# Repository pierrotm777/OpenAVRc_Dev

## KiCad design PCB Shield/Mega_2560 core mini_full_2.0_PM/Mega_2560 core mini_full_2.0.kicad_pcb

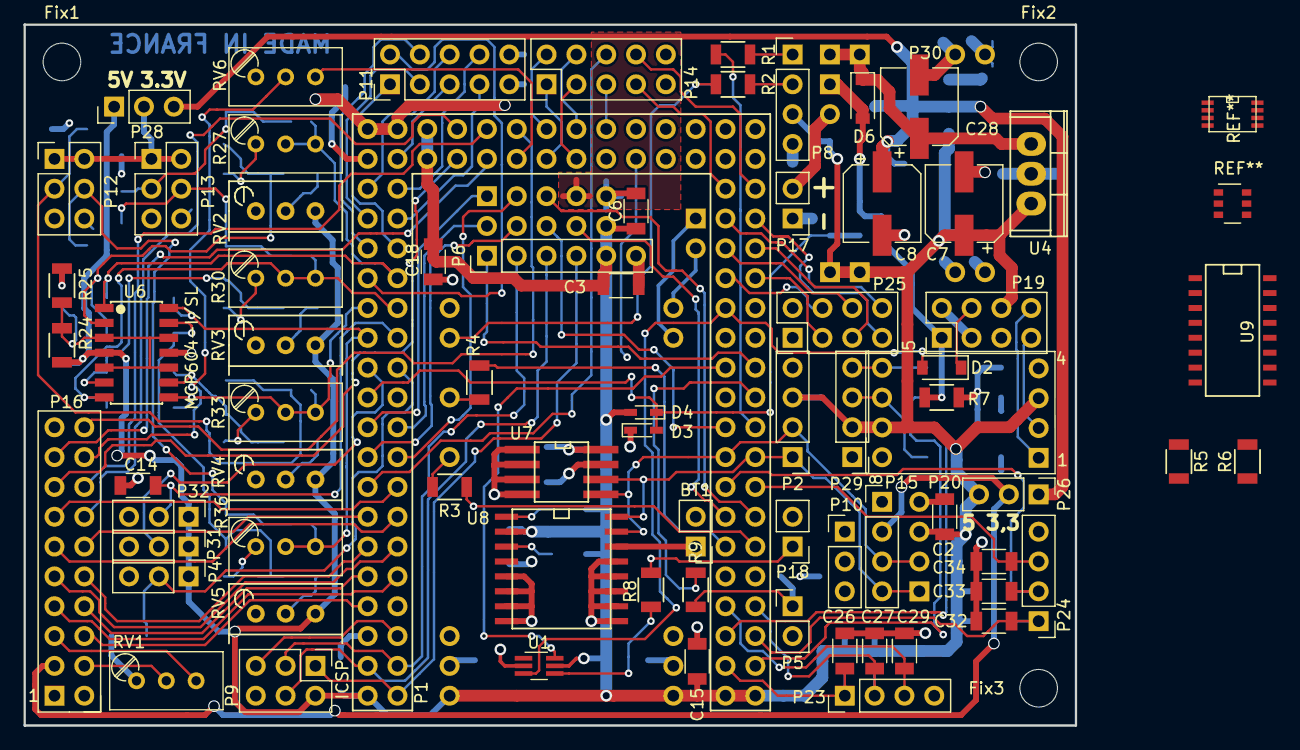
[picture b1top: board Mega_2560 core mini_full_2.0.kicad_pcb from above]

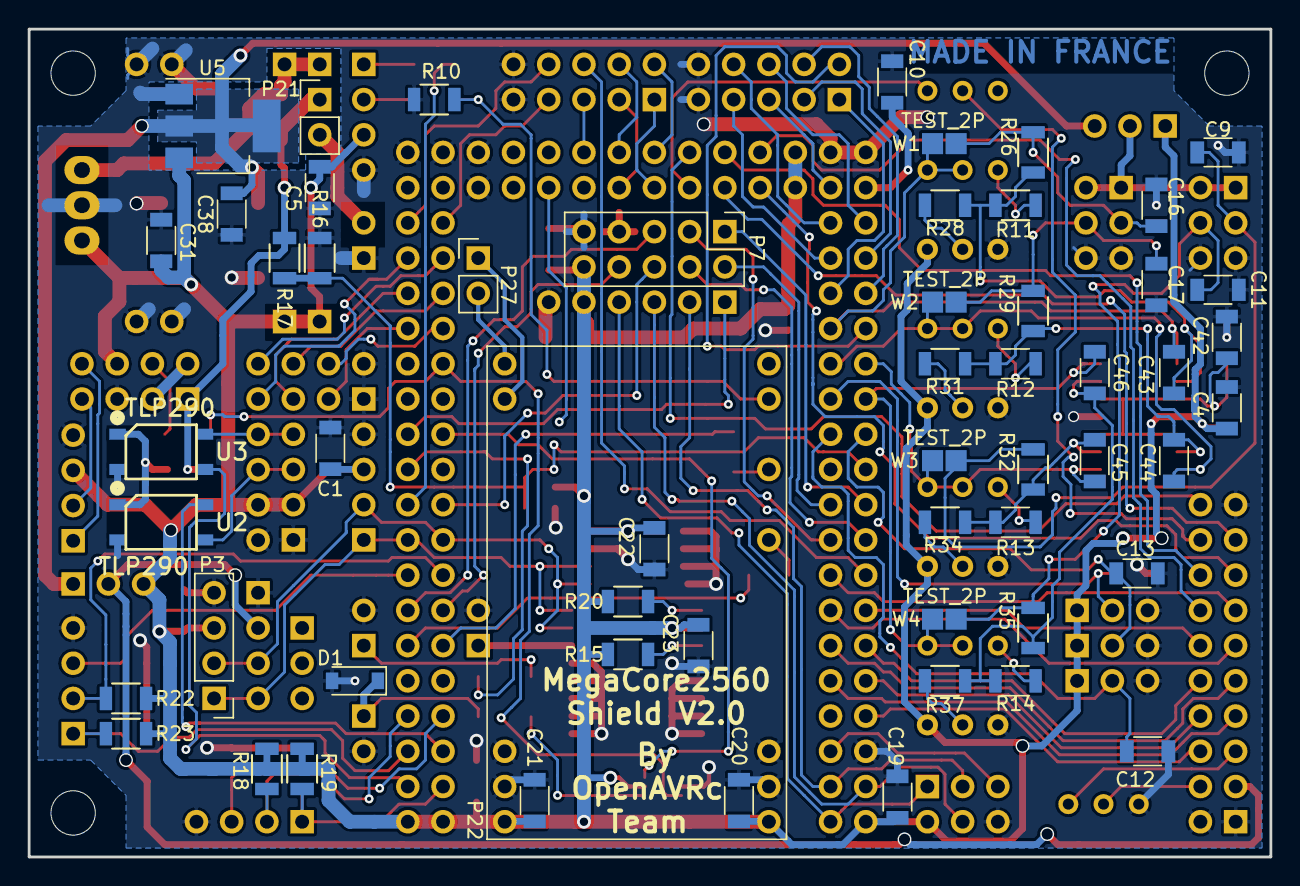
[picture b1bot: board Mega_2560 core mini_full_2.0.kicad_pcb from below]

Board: 2 copper layers, 89.5 x 59.7 mm, 133 parts (56 on the bottom side), 122 nets.

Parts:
BT1: CR2032; Pin_Header_Straight_1x02_Pitch2.54mm
C1, C2, C3, C5: 47nF; C_1206
C4, C6, C9, C10, C11, C12, C13, C14, C15, C16, C17, C18, C19, C20, C21, C22, C23, C26, C27, C29, C31, C32, C33, C34, C38: 100nF; C_1206
C7, C8, C28: 47µF; CP_Elec_6.3x5.3
C42: 6.8nF; C_1206
C43, C44, C45, C46: 22nF; C_1206
D1, D2, D6: MBR0520; D_SOD-123
D3, D4: LL4148; D_SCD80_HandSoldering
Fix1, Fix2, Fix3: MountingHole_3.2mm_M3
P1: 2560-core; Connectors-2560-core
P2: Clock; Pin_Header_Straight_1x04_Pitch2.54mm
P3: Option; Pin_Header_Straight_1x04_Pitch2.54mm
P4: Pot3; Pin_Header_Straight_1x03_Pitch2.54mm
P5: Vibreur; Pin_Header_Straight_1x02_Pitch2.54mm
P6: Micro_sd; Pin_Header_Straight_1x06_Pitch2.54mm
P7: SPIX; Pin_Header_Straight_2x05_Pitch2.54mm
P8: Audio; Pin_Header_Straight_1x04_Pitch2.54mm
P9: SPI; Pin_Header_Straight_2x03_Pitch2.54mm
P10: SPI_libre; Pin_Header_Straight_1x03_Pitch2.54mm
P11: Trim; Pin_Header_Straight_2x05_Pitch2.54mm
P12: Stick_left; Pin_Header_Straight_2x03_Pitch2.54mm
P13: Stick_right; Pin_Header_Straight_2x03_Pitch2.54mm
P14: Switch; Pin_Header_Straight_2x05_Pitch2.54mm
P15: LCD_I2C; Pin_Header_Straight_1x04_Pitch2.54mm
P16: LCD; Pin_Header_Straight_2x10_Pitch2.54mm
P17: BATT; Pin_Header_Straight_1x02_Pitch2.54mm
P18: Ecolage; Pin_Header_Straight_1x02_Pitch2.54mm
P19: Module_TX; Pin_Header_Straight_2x04_Pitch2.54mm
P20: TTL/RS232; Con_RS232_TTL
P21: Sw_power; Pin_Header_Straight_1x02_Pitch2.54mm
P22: CONN_JQ6500_28P_mini; connector_mini-JQ6500-28P
P23: Rot_1; Pin_Header_Straight_1x04_Pitch2.54mm
P24: Rot_2; Pin_Header_Straight_1x04_Pitch2.54mm
P25: Keys; Pin_Header_Straight_2x04_Pitch2.54mm
P26: LCD_Alim; Pin_Header_Straight_1x03_Pitch2.54mm
P27: HP; Pin_Header_Straight_1x02_Pitch2.54mm
P28: 5v/3,3v manches; Pin_Header_Straight_1x03_Pitch2.54mm
P29: RXTX; Pin_Header_Straight_1x04_Pitch2.54mm
P30: MiniDCDC3A
P31: Pot2; Pin_Header_Straight_1x03_Pitch2.54mm
P32: Pot1; Pin_Header_Straight_1x03_Pitch2.54mm
R1, R10: 22K; R_1206
R2, R4: 1K; R_1206
R3: 18K; R_1206
R5, R6, R15, R20, R26, R28, R29, R31, R32, R34, R35, R37: 10K; R_1206
R7: 470; R_1206
R8: 200; R_1206
R9: 220; R_1206
R11, R12, R13, R14: 15K; R_1206
R16: 2.7K; R_1206
R17: 5.1K; R_1206
R18, R19, R22, R23: 5.1k; R_1206
R24, R25: 33K; R_1206
R27, R30, R33, R36: POT_22k; Potentiometer_Trimmer_Bourns_3296W
RV1: 220K; Potentiometer_Trimmer_Bourns_3296W
RV2, RV3, RV4, RV5: POT_100k; Potentiometer_Bourns_3296W_3-8Zoll_Inline_ScrewUp
RV6: 22K; Potentiometer_Trimmer_Bourns_3296W
U1: 74LVC1G3157; SOT-363_SC-70-6_Handsoldering
U2, U3: TLP290; SOP4
U4: L4941; TO-220
U5: LD1117S33TR; SOT-223
U6: MCP604-I/SL; SOP14
U7: FM24W256; SOIC-8-FRAM_DI
U8: DS3231; SO-16-DS3231
U9: 4050; SO-16-N
W1, W2, W3, W4: TEST_2P; TESTPT

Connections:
+BATT: D6.2, P19.1, P21.1, R7.1, R17.2
/CS_A7105: P1.J6, P7.3
/CS_CC2500: P1.J3, P7.1
/CS_CYRF6936: P1.J4, P7.2
/CS_NRF24L01: P1.J5, P7.4
/DCDC_IN+: C28.1, D6.1, P30.3, P30.4, U4.1
/Isp_rst: P1.RST, P9.5
/JQ6500Busy: P1.J0, R3.1
/JQ6500Data: P1.J1, R4.1
/Key_DOWN: P1.L0, P25.4
/Key_ESC: P1.L5, P25.7
/Key_LEFT: P1.L3, P25.5
/Key_MENU: P1.L4, P25.8
/Key_RIGHT: P1.L2, P25.6
/Key_UP: P1.L1, P25.3
/LCD_VCC: P15.2, P16.3, P26.2
/LIPO+: P17.2, P21.2
/Lcd_A0: P1.C5, P16.16
/Lcd_bla: P1.C2, RV6.3
/Lcd_cs: P1.C3, P16.20
/Lcd_db0: P1.A0, P16.6
/Lcd_db1: P1.A1, P16.7
/Lcd_db2: P1.A2, P16.8
/Lcd_db3: P1.A3, P16.9
/Lcd_db4: P1.A4, P16.10
/Lcd_db5: P1.A5, P16.11
/Lcd_db6: P1.A6, P16.12
/Lcd_db7: P1.A7, P16.13
/Lcd_e: P1.C7, P16.14
/Lcd_r/w: P1.C6, P16.15
/Lcd_rst: P1.C4, P16.17
/Lcd_vo: P16.4, RV1.2
/Master_PPMout: D2.2, P1.B6, U1.3
/Microsd_CS: P1.B0, P6.1
/Miso: P1.B3, P6.4, P9.1
/Mosi: P1.B2, P6.3, P9.4
/PPM_TX_OUT: D2.1, P19.4
/PPM_in: P1.D4, U1.1
/Pot_1: C14.1, P1.AC12, P32.2
/Pot_2: C13.1, P1.AC13, P31.2
/Pot_3: C12.1, P1.AC14, P4.2
/Power_manches: P12.1, P12.2, P13.1, P13.2, P28.2
/RX_module: P19.8, P20.1
/Rot_1A: C29.1, P1.E4, P23.3
/Rot_1B: C27.1, P1.E5, P23.2, R18.2
/Rot_1push: C26.1, P1.G5, P23.1, R19.2
/Rot_2A: C34.1, P1.D2, P24.3
/Rot_2B: C33.1, P1.D3, P24.2, R22.2
/Rot_2push: C32.1, P1.E3, P24.1, R23.2
/SCL: P1.D0, P2.1, P3.1, P15.4, U7.6, U8.16
/SDA: P1.D1, P2.2, P3.2, P15.3, U7.5, U8.15
/Sck: P1.B1, P6.2, P9.3
/Sim_Control: P1.H6, U1.6
/Stick_LH: C46.1, P1.AC11, R36.2, R36.3, U6.14, W4.1
/Stick_LHcon: C11.1, P12.4, R35.2, W4.2
/Stick_LV: C45.1, P1.AC9, R33.2, R33.3, U6.8, W3.1
/Stick_LVcon: C9.1, P12.3, R32.2, W3.2
/Stick_RH: C43.1, P1.AC8, R27.2, R27.3, U6.1, W1.1
/Stick_RHcon: C16.1, P13.3, R26.2, W1.2
/Stick_RV: C44.1, P1.AC10, R30.2, R30.3, U6.7, W2.1
/Stick_RVcon: C17.1, P13.4, R29.2, W2.2
/Sw_ailDR: P1.D7, P14.5
/Sw_eleDR: P1.L6, P14.7
/Sw_gear: P1.G1, P14.4
/Sw_id1: P1.C0, P14.1
/Sw_id2: P1.C1, P14.2
/Sw_rudDR: P1.G0, P14.3
/Sw_thcut: P1.G2, P14.6
/Sw_turn: P1.L7, P14.8
/TX_module: P19.7, P20.2
/Tele_RX: P1.E0, U3.3
/Tele_TX: P1.E1, U2.4
/Trim_LH->: P1.AC6, P11.1
/Trim_LH<-: P1.AC7, P11.2
/Trim_LV->: P1.AC4, P11.7
/Trim_LV<-: P1.AC5, P11.4
/Trim_RH->: P1.AC0, P11.5
/Trim_RH<-: P1.AC1, P11.6
/Trim_RV->: P1.AC2, P11.8
/Trim_RV<-: P1.AC3, P11.3
/U_batt: D3.1, D4.2, P1.AC15, R16.2, R17.1
/VREF: C10.1, P1.VREF
/Vibreur: P1.H5, R9.2
/Xmitter_MISO: P1.H0, P7.5
/Xmitter_MOSI: P1.H1, P7.8
/Xmitter_SCK: P1.H2, P7.6
/audio_left_in: P1.H3, R1.2
/audio_right_in: P22.DACL, R2.2, R10.1
GND: BT1.2, C1.1, C2.1, C3.1, C4.2, C5.1, C6.2, C7.2, C8.2, C9.2, C10.2, C11.2, C12.2, C13.2, C14.2, C15.1, C16.2, C17.2, C18.1, C19.1, C20.2, C21.2, C22.2, C23.2, C26.2, C27.2, C28.2, C29.2, C31.2, C32.2, C33.2, C34.2, C38.2, C42.2, D1.2, D4.1, P1.GND, P2.4, P3.4, P4.3, P5.2, P6.6, P7.9, P8.4, P9.6, P11.9, P11.10, P12.5, P12.6, P13.5, P13.6, P14.9, P14.10, P15.1, P16.1, P16.2, P16.19, P17.1, P18.2, P19.5, P20.4, P20.8, P22.GND, P23.4, P24.4, P25.1, P25.2, P29.1, P30.1, P30.2, P30.7, P30.8, P31.3, P32.3, R10.2, R16.1, R25.2, RV1.1, RV2.1, RV3.1, RV4.1, RV5.1, U1.2, U2.2, U3.2, U4.2, U5.1, U6.11, U7.1, U7.2, U7.3, U7.4, U7.7, U8.5, U8.6, U8.7, U8.8, U8.9, U8.10, U8.11, U8.12, U8.13, U9.8
unnamed: BT1.1, U8.14
unnamed: C42.1, R24.2, R25.1, U6.3, U6.5, U6.10, U6.12
unnamed: C43.2, R11.2, R26.1, R28.1, U6.2
unnamed: C44.2, R12.2, R29.1, R31.1, U6.6
unnamed: C45.2, R13.2, R32.1, R34.1, U6.9
unnamed: C46.2, R14.2, R35.1, R37.1, U6.13
unnamed: D1.1, P5.1, R9.1
unnamed: P8.1, R1.1
unnamed: P8.2, R2.1
unnamed: P16.5, RV1.3
unnamed: P16.18, RV6.2
unnamed: P18.1, R8.1
unnamed: P19.2, P19.3
unnamed: P20.5, P29.4, U3.4
unnamed: P20.6, P29.3, U2.3
unnamed: P22.BUSY, R3.2
unnamed: P22.RX, R4.2
unnamed: P22.SPK+, P27.2
unnamed: P22.SPK-, P27.1
unnamed: R7.2, U2.1, U3.1
unnamed: R8.2, U1.4
unnamed: R11.1, R27.1
unnamed: R12.1, R30.1
unnamed: R13.1, R33.1
unnamed: R14.1, R36.1
unnamed: R15.1, U8.3
unnamed: R20.1, U8.1
unnamed: R28.2, RV2.2
unnamed: R31.2, RV3.2
unnamed: R34.2, RV4.2
unnamed: R37.2, RV5.2
P3_3V: C8.1, C38.1, P7.7, P26.1, P28.3, U5.2, U5.4, U9.1
VCC: C1.2, C2.2, C3.2, C4.1, C5.2, C6.1, C7.1, C15.2, C18.2, C19.2, C20.1, C21.1, C22.1, C23.1, C31.1, D3.2, P1.VCC, P2.3, P3.3, P4.1, P6.5, P7.10, P8.3, P9.2, P19.6, P20.3, P20.7, P22.VCC, P26.3, P28.1, P29.2, P30.5, P30.6, P31.1, P32.1, R15.2, R18.1, R19.1, R20.2, R22.1, R23.1, R24.1, RV2.3, RV3.3, RV4.3, RV5.3, U1.5, U4.3, U5.3, U6.4, U7.8, U8.2

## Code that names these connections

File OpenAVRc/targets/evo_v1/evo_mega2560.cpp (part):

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  key_pressed = (bool)((~GPIO_KEYB_MATRIX_COL) & (INP_K_KEYB_COL_A | INP_K_KEYB_COL_B | INP_K_KEYB_COL_C));

  if(key_matrix_row_previous == OUT_J_KEYB_ROW_A) {
    keys[KEY_LEFT].input( (GPIO_KEYB_MATRIX_COL & INP_K_KEYB_COL_A) ? 0 :1); //Spanner icon - (setup)
    keys[KEY_RIGHT].input( (GPIO_KEYB_MATRIX_COL & INP_K_KEYB_COL_B) ? 0 :1); //Joystick icon - (controls)
  }
  else if(key_matrix_row_previous == OUT_J_KEYB_ROW_B) {
    //if(GPIO_KEYB_MATRIX_COL & INP_K_KEYB_COL_A) incRotaryEncoder(1, +1); // test code
    //if(GPIO_KEYB_MATRIX_COL & INP_K_KEYB_COL_B) incRotaryEncoder(1, -1); // test code
  }
  else if(key_matrix_row_previous == OUT_J_KEYB_ROW_C) {
    keys[KEY_DOWN].input( (GPIO_KEYB_MATRIX_COL & INP_K_KEYB_COL_A) ? 0 :1); //Down arrow
    keys[KEY_UP].input( (GPIO_KEYB_MATRIX_COL & INP_K_KEYB_COL_B) ? 0 :1); //Up arrow
    keys[KEY_MENU].input( (GPIO_KEYB_MATRIX_COL & INP_K_KEYB_COL_C) ? 0 :1); //Enter
  }
  else if(key_matrix_row_previous == OUT_J_KEYB_ROW_D) {
    keys[KEY_EXIT].input( (GPIO_KEYB_MATRIX_COL & INP_K_KEYB_COL_A) ? 0 :1); //Rev/clr
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
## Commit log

2017-08-27 Update_Mega_2560 core mini_full_2.0_PM_23-8-2017
2017-09-03 V1.15 F-ram
    Latest eeprom V217 release
2017-09-03 V1.15 F-ram setup
2017-09-04 Remove test setup
2017-09-04 Revert "Remove test setup"
    This reverts commit 04d635bcb7344f00ca8d6327a58d30a25aff24d9.
2017-09-06 Just fix error and warnings for evo build.
2017-09-07 Update_Mega_2560 core mini_full_2.0_PM_7-9-2017
2017-09-08 telemetry type export/import was missing. Thanks JPZ
2017-09-08 New Setup 1.15 F-ram
2017-09-09 Use PROGMEM for Evo switches code.
2017-09-10 Update cablind documentation file
2017-09-10 I/O update
2017-09-10 wxsmith sync
2017-09-10 New V1.15 setup
2017-09-10 Move SDCARD chip select #defines into board.h files.
2017-09-27 Update documention file (add 4 ways ALPS trims infos)
2017-10-02 Update Master branch for internationalization
2017-10-02 Update Makefile version
2017-10-04 Simu color Bug in V1.15
2017-10-04 Desktop Gui arrangment for English language
2017-10-04 Multilanguage setup V1.15
2017-10-08 New Setup include latest MSYS.Dll
2017-10-22 Add SH1106 suport
2017-11-05 Update schematic R values
2017-11-05 Add pdf fabrication files
2017-11-30 Create MegaCore LM386 amplifier repository
2017-11-30 First save MegaCore LM386 amplifier files
2017-11-30 Update documentation
    Change text on page 9.
2017-12-01 Setup : En Voice file from ElectoPete (Rcgroups)
2021-02-06 Remove unused files
2021-02-06 Remove bad codes, add Joystick le3dp code
2021-02-07 modifie file in README.md
2021-02-07 Update README.md
    Add model step
2021-03-02 Update with new code
2021-03-02 Add OpenAVRcBT_HeadTrackerFW project
2021-03-02 Solve PPM issue
2021-03-02 add led option for Pro Micro, add undefine on ISR
2026-03-19 Update uCli.cpp
    Corrections étiquette XMODEM
2026-03-19 try to debug xmodem

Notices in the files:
OpenAVRc/targets/evo_v1/evo_mega2560.cpp:
This program is free software; you can redistribute it and/or modify
it under the terms of the GNU General Public License version 2 as
published by the Free Software Foundation.
